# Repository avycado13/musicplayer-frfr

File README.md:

# Music Player

I built a music player that's powered by a seeed studio xiao rp2350 devboard and a dfplayer mini.
My initial goal was to just build something, like literally anything, for Kai's speedrun huddle and i realized it would be cool to have a music player that i could take places without bringing my phone. I learnt alot about PCB design and i used this cool plugin called (KiCad Routing tools)[https://github.com/drandyhaas/KiCadRoutingTools] it sped up routing a lot because i just had to layout the parts and didnt have to painstakingly look through where each one goes.

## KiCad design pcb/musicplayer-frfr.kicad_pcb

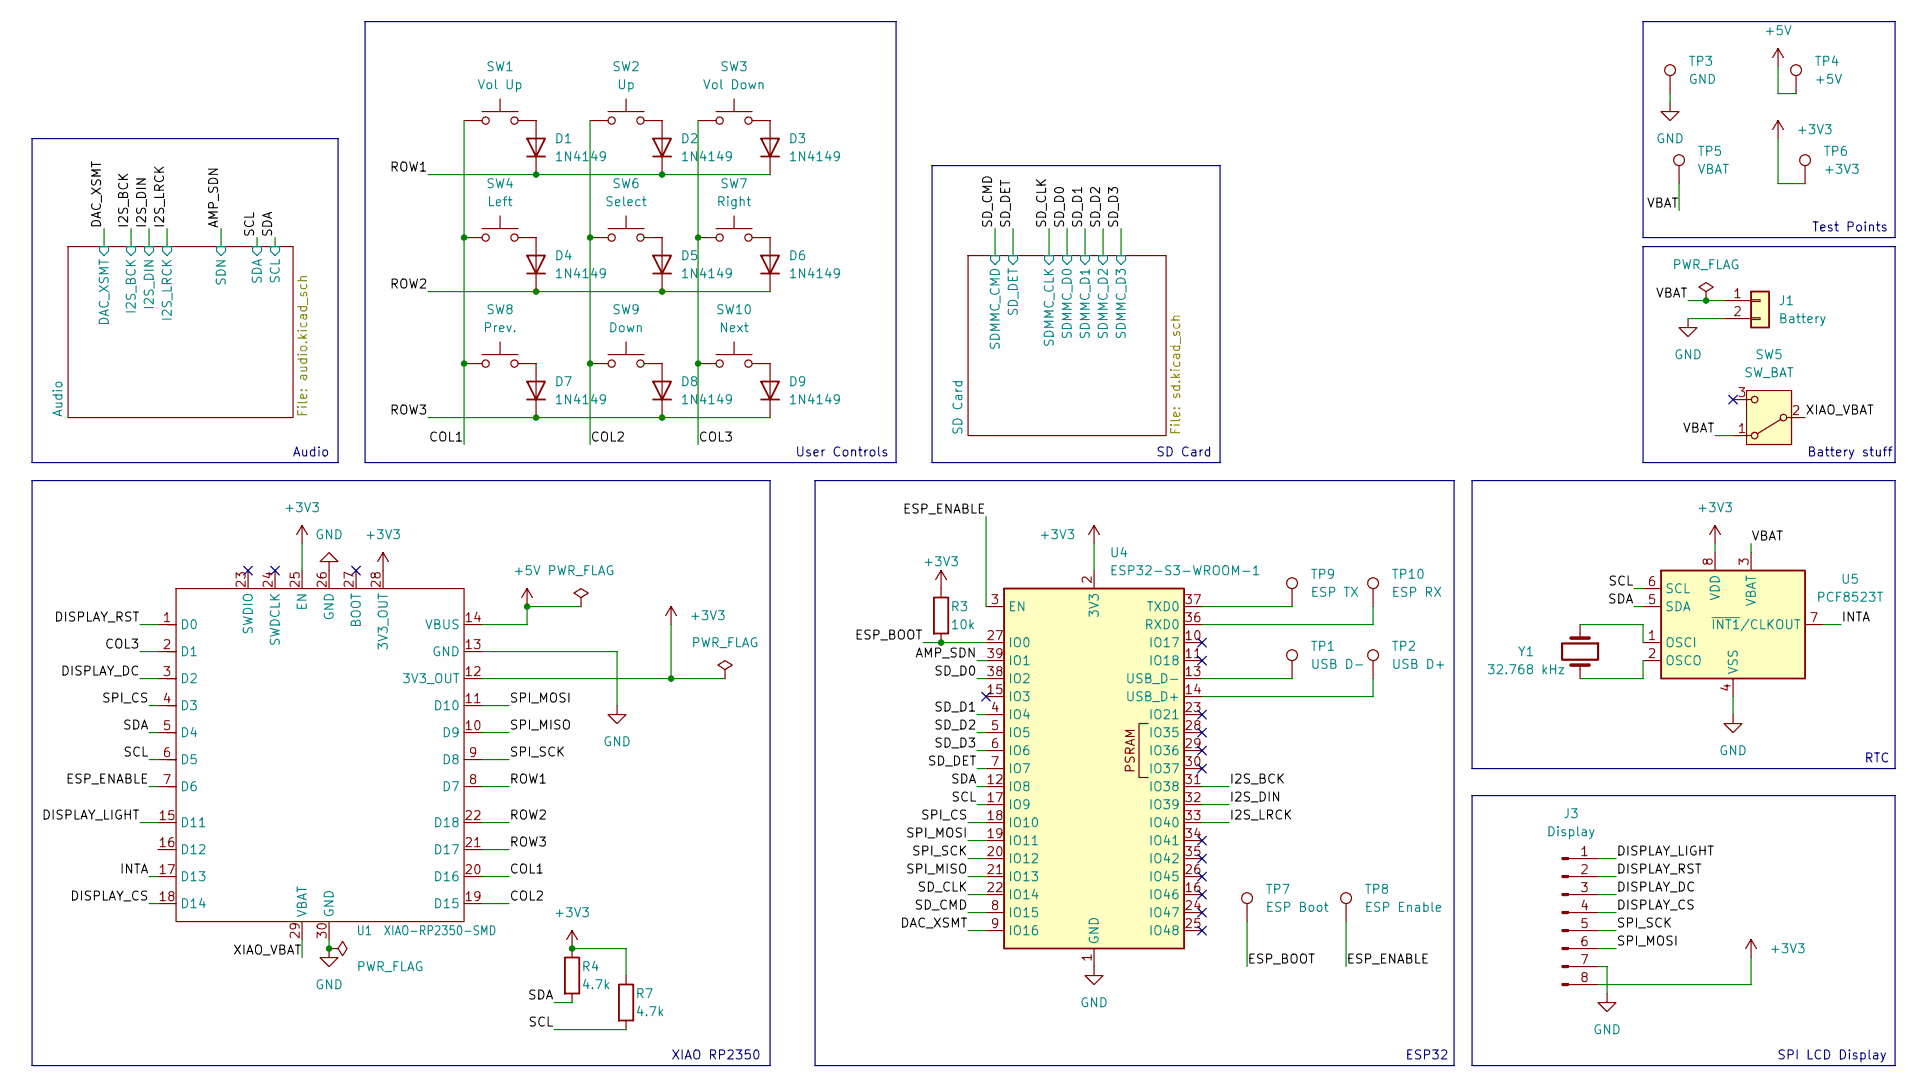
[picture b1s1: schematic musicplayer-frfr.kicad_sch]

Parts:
D1, D2, D3, D4, D5, D6, D7, D8, D9: 1N4149; D_DO-35_SOD27_P7.62mm_Horizontal
J1: Battery; JST_PH_S2B-PH-K_1x02_P2.00mm_Horizontal; MPN S2B-PH-K-S; LCSC PN C157932
J3: Display; PinHeader_1x08_P2.54mm_Vertical
R3: 10k; R_0805_2012Metric_Pad1.20x1.40mm_HandSolder
R4, R7: 4.7k; R_0805_2012Metric_Pad1.20x1.40mm_HandSolder
SW1: Vol Up; SW_PUSH_6mm; MPN TS4550CJ; LCSC PN C557612
SW2: Up; SW_PUSH_6mm; MPN TS4550CJ; LCSC PN C557612
SW3: Vol Down; SW_PUSH_6mm; MPN TS4550CJ; LCSC PN C557612
SW4: Left; SW_PUSH_6mm; MPN TS4550CJ; LCSC PN C557612
SW5: SW_BAT; SW_Slide_SPDT_Straight_CK_OS102011MS2Q; MPN OS102011MS2QN1; LCSC PN C221829
SW6: Select; SW_PUSH_6mm; MPN TS4550CJ; LCSC PN C557612
SW7: Right; SW_PUSH_6mm; MPN TS4550CJ; LCSC PN C557612
SW8: Prev.; SW_PUSH_6mm; MPN TS4550CJ; LCSC PN C557612
SW9: Down; SW_PUSH_6mm; MPN TS4550CJ; LCSC PN C557612
SW10: Next; SW_PUSH_6mm; MPN TS4550CJ; LCSC PN C557612
TP1: USB D-; TestPoint_Pad_D3.0mm
TP2: USB D+; TestPoint_Pad_D3.0mm
TP3: GND; TestPoint_Pad_D3.0mm
TP4: +5V; TestPoint_Pad_D3.0mm
TP5: VBAT; TestPoint_Pad_D3.0mm
TP6: +3V3; TestPoint_Pad_D3.0mm
TP7: ESP Boot; TestPoint_Pad_D3.0mm
TP8: ESP Enable; TestPoint_Pad_D3.0mm
TP9: ESP TX; TestPoint_Pad_D3.0mm
TP10: ESP RX; TestPoint_Pad_D3.0mm
U1: XIAO-RP2350-SMD; MPN 102010550; LCSC PN C41882923
U4: ESP32-S3-WROOM-1
U5: PCF8523T; SOIC-8_3.9x4.9mm_P1.27mm
Y1: 32.768 kHz; Crystal_SMD_2012-2Pin_2.0x1.2mm_HandSoldering

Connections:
+3V3: J3.8, R3.1, R4.1, R7.1, TP6.1 (1_1), U1.12 (3V3_OUT), U1.25 (EN), U1.28 (3V3_OUT), U4.2 (3V3), U5.8 (VDD); also elsewhere on the board
+5V: TP4.1 (1_1), U1.14 (VBUS)
/AMP_SDN: U4.39 (IO1); also elsewhere on the board
/COL1: SW1.1, SW4.1, SW8.1, U1.20 (D16)
/COL2: SW2.1, SW6.1, SW9.1, U1.19 (D15)
/COL3: SW3.1, SW7.1, SW10.1, U1.2 (D1)
/DAC_XSMT: U4.9 (IO16); also elsewhere on the board
/DISPLAY_CS: J3.4, U1.18 (D14)
/DISPLAY_DC: J3.3, U1.3 (D2)
/DISPLAY_LIGHT: J3.1, U1.15 (D11)
/DISPLAY_RST: J3.2, U1.1 (D0)
/ESP_BOOT: R3.2, TP7.1 (1_1), U4.27 (IO0)
/ESP_ENABLE: TP8.1 (1_1), U1.7 (D6), U4.3 (EN)
/I2S_BCK: U4.31 (IO38); also elsewhere on the board
/I2S_DIN: U4.32 (IO39); also elsewhere on the board
/I2S_LRCK: U4.33 (IO40); also elsewhere on the board
/INTA: U1.17 (D13), U5.7 (~INT1/CLKOUT)
/ROW1: D1.1 (K), D2.1 (K), D3.1 (K), U1.8 (D7)
/ROW2: D4.1 (K), D5.1 (K), D6.1 (K), U1.22 (D18)
/ROW3: D7.1 (K), D8.1 (K), D9.1 (K), U1.21 (D17)
/SCL: R7.2, U1.6 (D5), U4.17 (IO9), U5.6 (SCL); also elsewhere on the board
/SDA: R4.2, U1.5 (D4), U4.12 (IO8), U5.5 (SDA); also elsewhere on the board
/SD_CLK: U4.22 (IO14); also elsewhere on the board
/SD_CMD: U4.8 (IO15); also elsewhere on the board
/SD_D0: U4.38 (IO2); also elsewhere on the board
/SD_D1: U4.4 (IO4); also elsewhere on the board
/SD_D2: U4.5 (IO5); also elsewhere on the board
/SD_D3: U4.6 (IO6); also elsewhere on the board
/SD_DET: U4.7 (IO7); also elsewhere on the board
/SPI_CS: U1.4 (D3), U4.18 (IO10)
/SPI_MISO: U1.10 (D9), U4.21 (IO13)
/SPI_MOSI: J3.6, U1.11 (D10), U4.19 (IO11)
/SPI_SCK: J3.5, U1.9 (D8), U4.20 (IO12)
/VBAT: J1.1, SW5.1 (A), TP5.1 (1_1), U5.3 (VBAT)
/XIAO_VBAT: SW5.2 (B), U1.29 (VBAT)
GND: J1.2, J3.7, TP3.1 (1_1), U1.13 (GND), U1.26 (GND), U1.30 (GND), U4.1 (GND), U4.40 (GND), U4.41 (GND), U5.4 (VSS); also elsewhere on the board
unnamed: D1.2 (A), SW1.2
unnamed: D2.2 (A), SW2.2
unnamed: D3.2 (A), SW3.2
unnamed: D4.2 (A), SW4.2
unnamed: D5.2 (A), SW6.2
unnamed: D6.2 (A), SW7.2
unnamed: D7.2 (A), SW8.2
unnamed: D8.2 (A), SW9.2
unnamed: D9.2 (A), SW10.2
unnamed: TP10.1 (1_1), U4.36 (RXD0)
unnamed: TP9.1 (1_1), U4.37 (TXD0)
unnamed: TP2.1 (1_1), U4.14 (USB_D+)
unnamed: TP1.1 (1_1), U4.13 (USB_D-)
unnamed: U5.1 (OSCI), Y1.1
unnamed: U5.2 (OSCO), Y1.2

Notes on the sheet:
Audio
Battery stuff
XIAO RP2350
Test Points
SD Card
RTC
ESP32
User Controls
SPI LCD Display

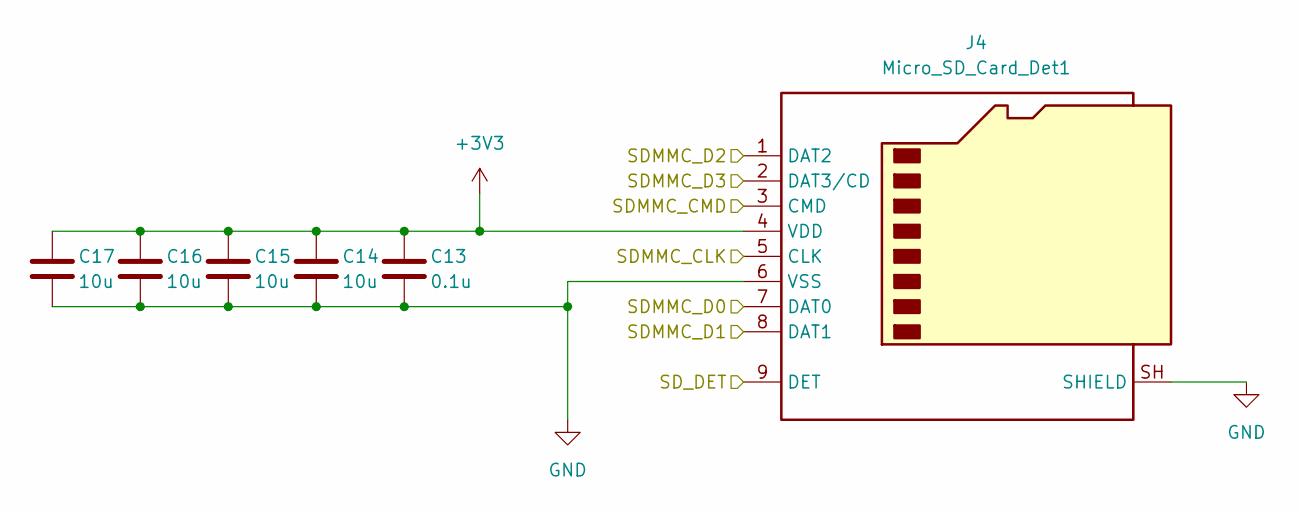
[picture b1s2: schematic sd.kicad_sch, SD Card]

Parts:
C13: 0.1u; C_0805_2012Metric_Pad1.18x1.45mm_HandSolder
C14, C15, C16, C17: 10u; C_0805_2012Metric_Pad1.18x1.45mm_HandSolder
J4: Micro_SD_Card_Det1; microSD_HC_Hirose_DM3AT-SF-PEJM5

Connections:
+3V3: C13.1, C14.1, C15.1, C16.1, C17.1, J4.4 (VDD); also elsewhere on the board
/SD_CLK: J4.5 (CLK); also elsewhere on the board
/SD_CMD: J4.3 (CMD); also elsewhere on the board
/SD_D0: J4.7 (DAT0); also elsewhere on the board
/SD_D1: J4.8 (DAT1); also elsewhere on the board
/SD_D2: J4.1 (DAT2); also elsewhere on the board
/SD_D3: J4.2 (DAT3/CD); also elsewhere on the board
/SD_DET: J4.9 (DET); also elsewhere on the board
GND: C13.2, C14.2, C15.2, C16.2, C17.2, J4.6 (VSS), J4.SH (SHIELD); also elsewhere on the board

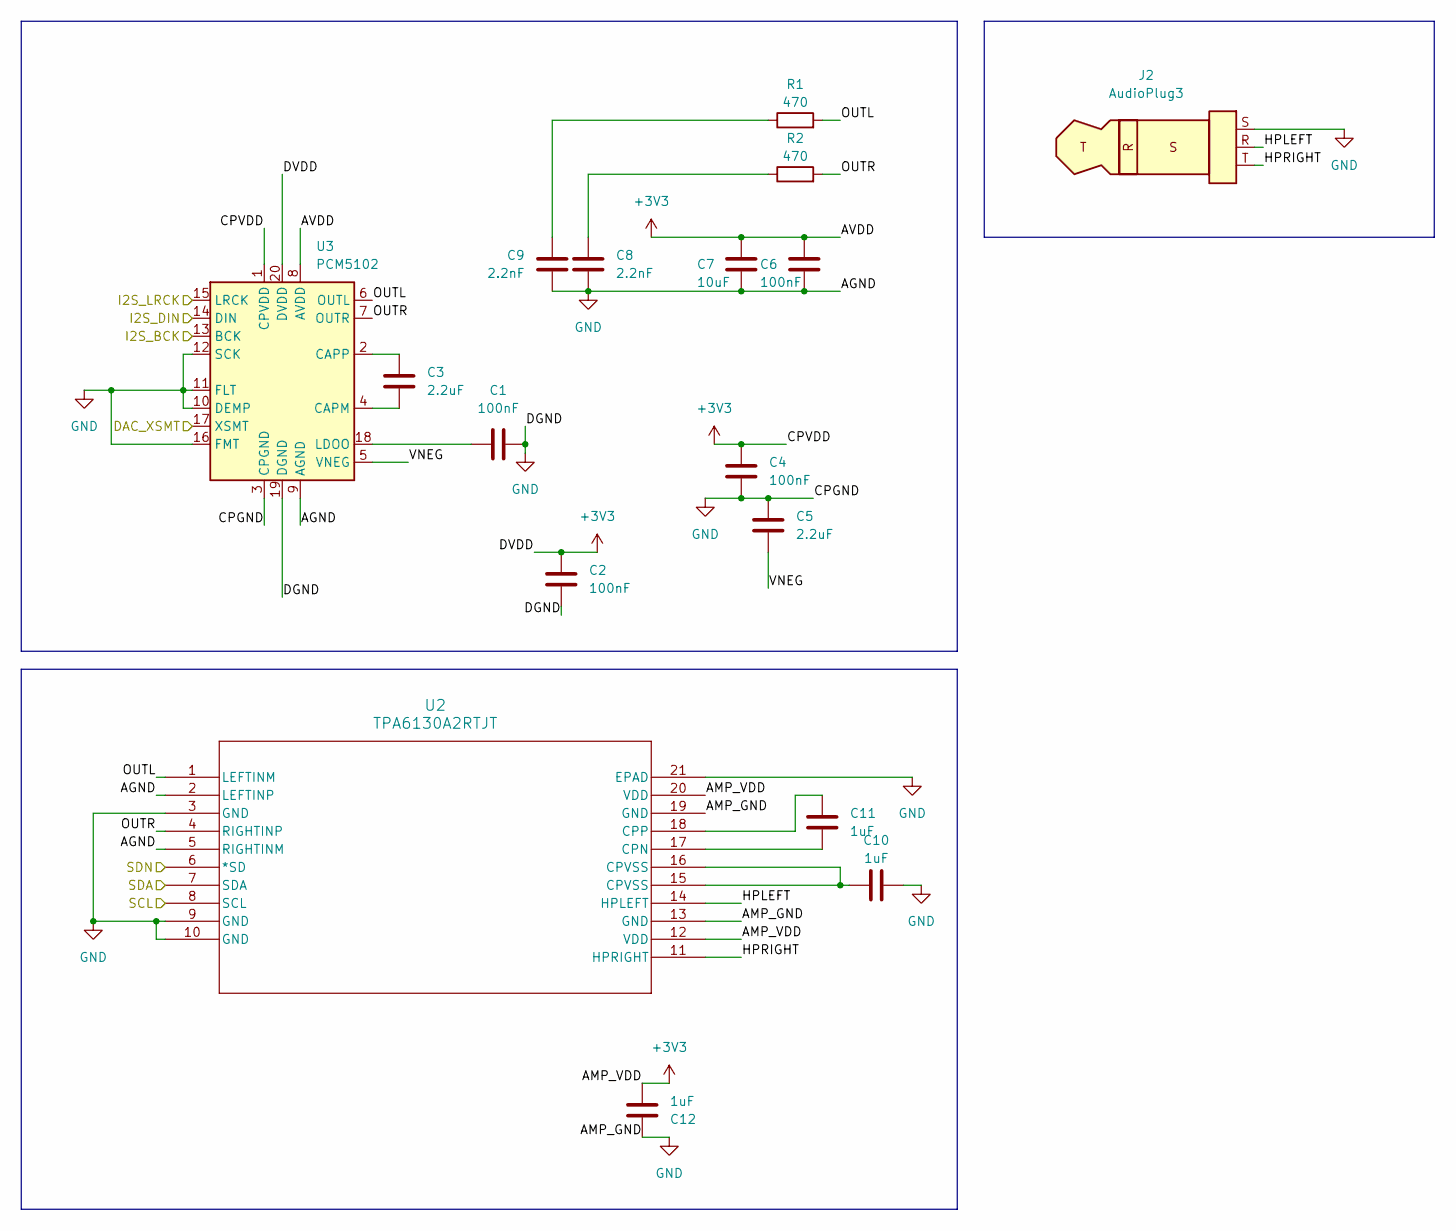
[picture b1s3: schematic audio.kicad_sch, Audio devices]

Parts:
C1, C2, C4, C6: 100nF; C_0805_2012Metric_Pad1.18x1.45mm_HandSolder
C3, C5: 2.2uF; C_0805_2012Metric_Pad1.18x1.45mm_HandSolder
C7: 10uF; C_0805_2012Metric_Pad1.18x1.45mm_HandSolder
C8, C9: 2.2nF; C_0805_2012Metric_Pad1.18x1.45mm_HandSolder
C10, C11, C12: 1uF; C_0805_2012Metric_Pad1.18x1.45mm_HandSolder
J2: AudioPlug3; Jack_3.5mm_CUI_SJ-3523-SMT_Horizontal; MPN SJ-3523-SMT-TR; LCSC PN C4991872
R1, R2: 470; R_0805_2012Metric_Pad1.20x1.40mm_HandSolder
U2: TPA6130A2RTJT; RTJ20_2P7X2P7
U3: PCM5102; TSSOP-20_4.4x6.5mm_P0.65mm

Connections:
+3V3: C2.2, C4.2, C6.2, C7.2, C12.1, U2.12 (VDD), U2.20 (VDD), U3.1 (CPVDD), U3.8 (AVDD), U3.20 (DVDD); also elsewhere on the board
/AMP_SDN: U2.6 (*SD); also elsewhere on the board
/Audio/HPLEFT: J2.R, U2.14 (HPLEFT)
/Audio/HPRIGHT: J2.T, U2.11 (HPRIGHT)
/Audio/OUTL: R1.2, U2.1 (LEFTINM), U3.6 (OUTL)
/Audio/OUTR: R2.2, U2.4 (RIGHTINP), U3.7 (OUTR)
/Audio/VNEG: C5.1, U3.5 (VNEG)
/DAC_XSMT: U3.17 (XSMT); also elsewhere on the board
/I2S_BCK: U3.13 (BCK); also elsewhere on the board
/I2S_DIN: U3.14 (DIN); also elsewhere on the board
/I2S_LRCK: U3.15 (LRCK); also elsewhere on the board
/SCL: U2.7 (SDA); also elsewhere on the board
/SDA: U2.8 (SCL); also elsewhere on the board
GND: C1.2, C2.1, C4.1, C5.2, C6.1, C7.1, C8.1, C9.2, C10.2, C12.2, J2.S, U2.2 (LEFTINP), U2.3 (GND), U2.5 (RIGHTINM), U2.9 (GND), U2.10 (GND), U2.13 (GND), U2.19 (GND), U2.21 (EPAD), U3.3 (CPGND), U3.9 (AGND), U3.10 (DEMP), U3.11 (FLT), U3.12 (SCK), U3.16 (FMT), U3.19 (DGND); also elsewhere on the board
unnamed: C8.2, R2.1
unnamed: C9.1, R1.1
unnamed: C10.1, U2.15 (CPVSS), U2.16 (CPVSS)
unnamed: C11.2, U2.17 (CPN)
unnamed: C11.1, U2.18 (CPP)
unnamed: C3.1, U3.4 (CAPM)
unnamed: C3.2, U3.2 (CAPP)
unnamed: C1.1, U3.18 (LDOO)

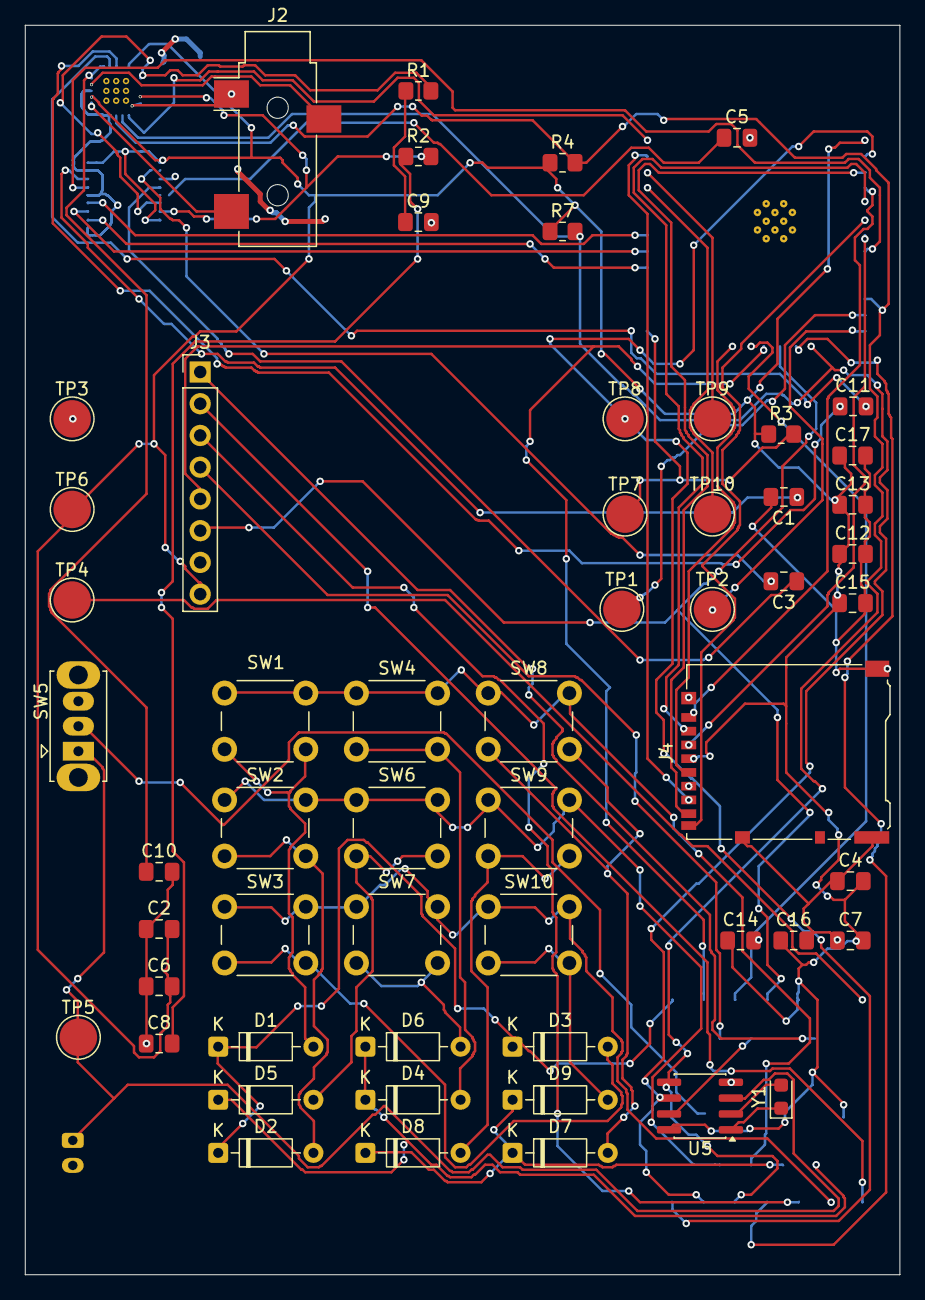
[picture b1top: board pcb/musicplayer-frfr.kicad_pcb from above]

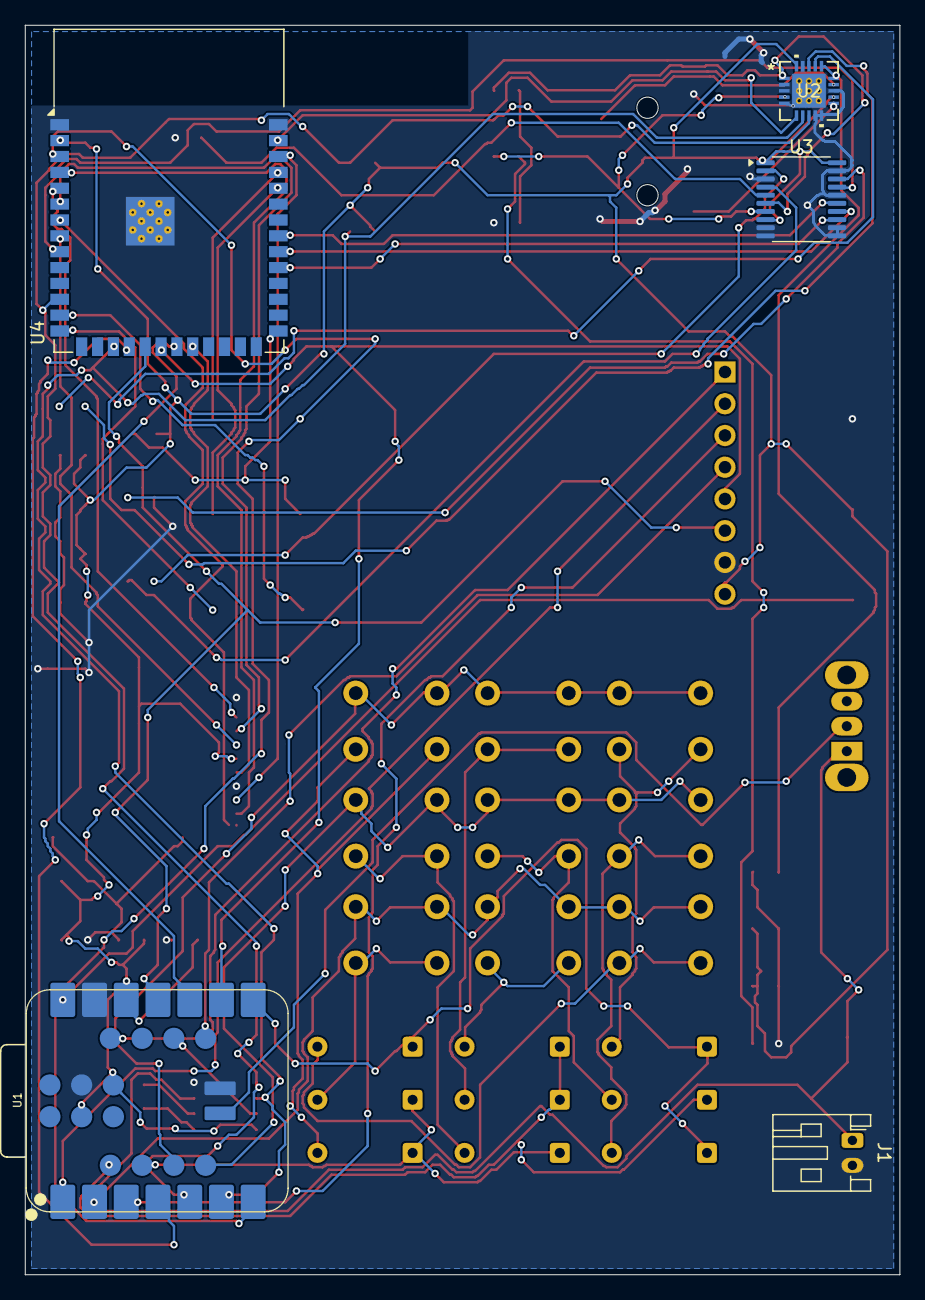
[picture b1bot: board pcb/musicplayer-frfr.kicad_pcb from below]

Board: 2 copper layers, 70.0 x 100.0 mm, 61 parts (5 on the bottom side), 64 nets.

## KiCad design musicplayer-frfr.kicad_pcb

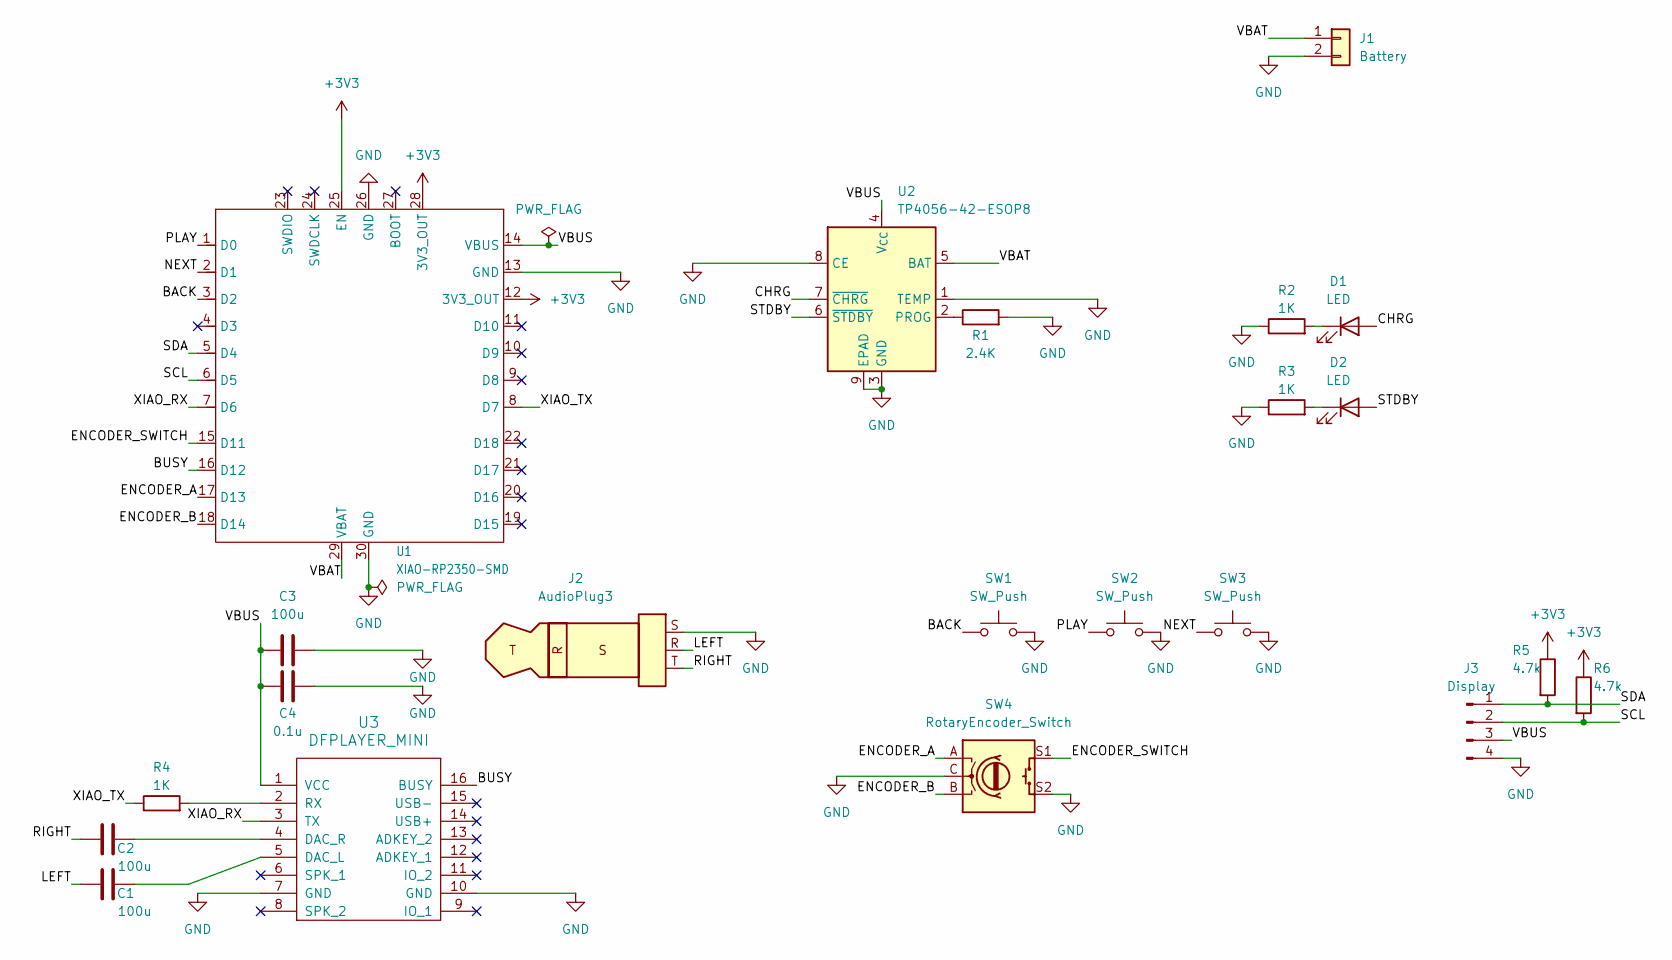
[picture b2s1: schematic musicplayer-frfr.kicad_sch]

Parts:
C1, C2, C3: 100u; CP_Radial_D6.3mm_P2.50mm
C4: 0.1u; C_0805_2012Metric
D1, D2: LED; LED_0805_2012Metric
J1: Battery; JST_PH_S2B-PH-K_1x02_P2.00mm_Horizontal
J2: AudioPlug3; Jack_3.5mm_CUI_SJ-3523-SMT_Horizontal
J3: Display; PinHeader_1x04_P2.54mm_Vertical
R1: 2.4K; R_0805_2012Metric
R2, R3, R4: 1K; R_0805_2012Metric
R5, R6: 4.7k; R_0805_2012Metric
SW1, SW2, SW3: SW_Push; SW_PUSH_6mm
SW4: RotaryEncoder_Switch; RotaryEncoder_Alps_EC11E-Switch_Vertical_H20mm
U1: XIAO-RP2350-SMD
U2: TP4056-42-ESOP8; SOIC-8-1EP_3.9x4.9mm_P1.27mm_EP2.41x3.3mm_ThermalVias
U3: DFPLAYER_MINI; DFPlayer_V2

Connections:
+3V3: R5.1, R6.1, U1.12 (3V3_OUT), U1.25 (EN), U1.28 (3V3_OUT)
/BACK: SW1.1, U1.3 (D2)
/BUSY: U1.16 (D12), U3.16 (BUSY)
/CHRG: D1.2 (A), U2.7 (~CHRG)
/ENCODER_A: SW4.A, U1.17 (D13)
/ENCODER_B: SW4.B, U1.18 (D14)
/ENCODER_SWITCH: SW4.S1, U1.15 (D11)
/LEFT: C1.2, J2.R
/NEXT: SW3.1, U1.2 (D1)
/PLAY: SW2.1, U1.1 (D0)
/RIGHT: C2.2, J2.T
/SCL: J3.2 (SCL), R6.2, U1.6 (D5)
/SDA: J3.1 (SDA), R5.2, U1.5 (D4)
/STDBY: D2.2 (A), U2.6 (~STDBY)
/VBAT: J1.1, U1.29 (VBAT), U2.5 (BAT)
/VBUS: C3.1, C4.1, J3.3 (VCC), U1.14 (VBUS), U2.4 (V_{CC}), U3.1 (VCC)
/XIAO_RX: U1.7 (D6), U3.3 (TX)
/XIAO_TX: R4.1, U1.8 (D7)
GND: C3.2, C4.2, J1.2, J2.S, J3.4 (GND), R1.2, R2.1, R3.1, SW1.2, SW2.2, SW3.2, SW4.C, SW4.S2, U1.13 (GND), U1.26 (GND), U1.30 (GND), U2.1 (TEMP), U2.3 (GND), U2.8 (CE), U2.9 (EPAD), U3.7 (GND), U3.10 (GND)
unnamed: D1.1 (K), R2.2
unnamed: D2.1 (K), R3.2
unnamed: R1.1, U2.2 (PROG)
unnamed: C1.1, U3.5 (DAC_L)
unnamed: C2.1, U3.4 (DAC_R)
unnamed: R4.2, U3.2 (RX)

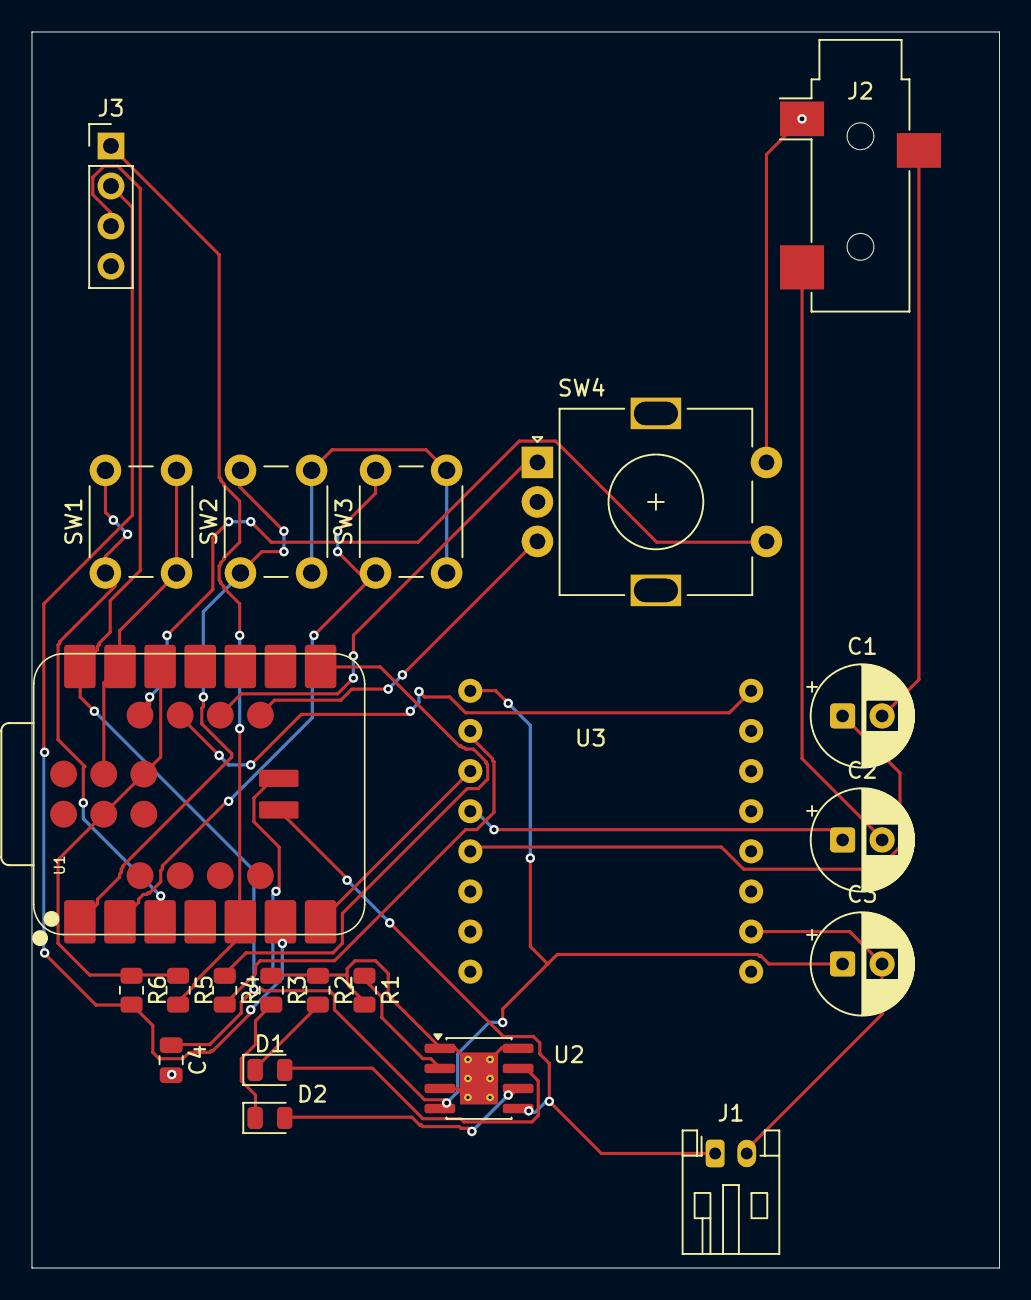
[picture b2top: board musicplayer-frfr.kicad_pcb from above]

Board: 2 copper layers, 61.2 x 78.2 mm, 22 parts (0 on the bottom side), 25 nets.

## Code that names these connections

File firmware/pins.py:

# GPIO assignments for the XIAO RP2350, derived from the schematic net labels
# in pcb/musicplayer-frfr.kicad_sch and the XIAO RP2350 pin multiplexing table:
# https://wiki.seeedstudio.com/XIAO_RP2350_Pin_Multiplexing/
#
# D0-D10 use the same GPIO mapping as XIAO RP2040. D11-D14 are the extra
# castellated pads on the back of the SMD module (verify against your build
# before trusting these if anything doesn't respond).

PLAY = 26             # D0  - PLAY button
NEXT = 27             # D1  - NEXT button
BACK = 28             # D2  - BACK button

SDA = 6               # D4  - unused for now, broken out for future I2C
SCL = 7               # D5  - unused for now, broken out for future I2C

DFPLAYER_RX = 0       # D6  - XIAO RX  <- DFPlayer TX
DFPLAYER_TX = 1       # D7  - XIAO TX  -> DFPlayer RX

ENCODER_SWITCH = 21   # D11 - rotary encoder push button
DFPLAYER_BUSY = 20    # D12 - DFPlayer BUSY line (low while playing)
ENCODER_A = 17        # D13 - rotary encoder A
ENCODER_B = 16        # D14 - rotary encoder B
